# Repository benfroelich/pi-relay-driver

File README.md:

# 3.3V control relay driver board for switching light AC/DC loads

https://oshpark.com/shared_projects/c22zDmKN

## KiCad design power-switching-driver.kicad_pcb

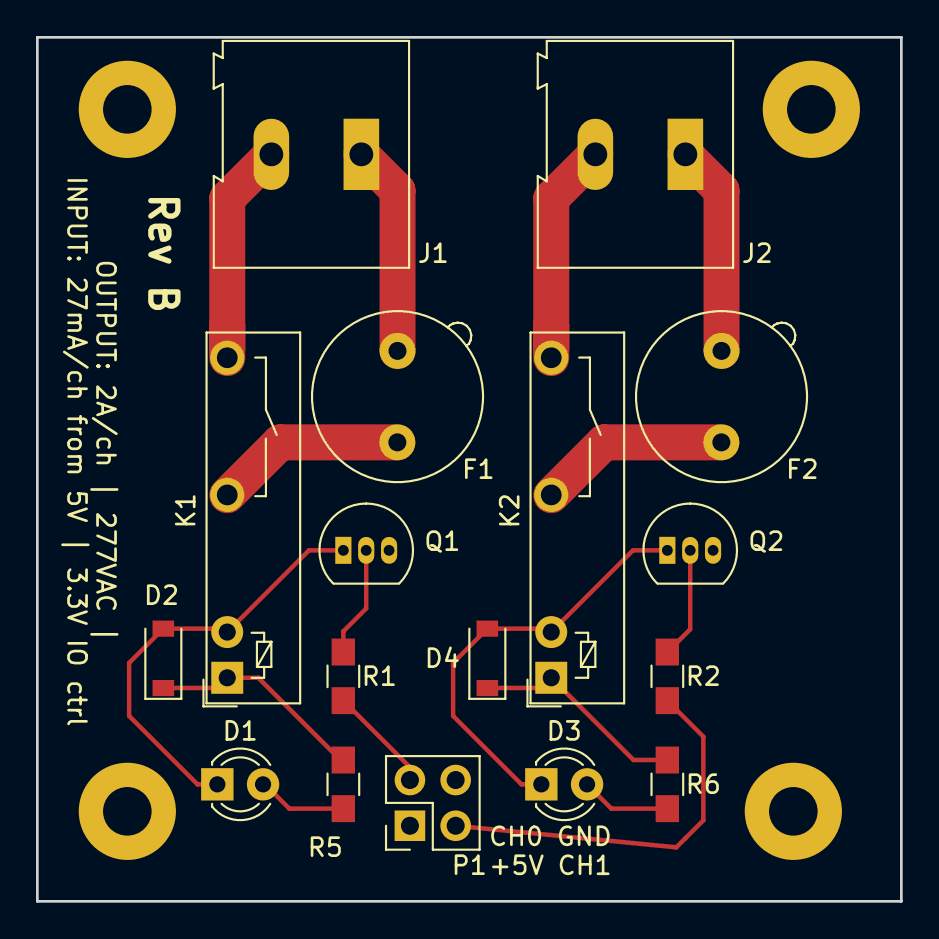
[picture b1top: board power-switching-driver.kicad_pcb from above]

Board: 2 copper layers, 48.0 x 48.0 mm, 17 parts (0 on the bottom side), 16 nets.

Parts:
D1, D3: LED; LED_D3.0mm
D2, D4: D; D_SOD-123
F1, F2: FUSE; Fuseholder_Fuse_TR5_Littlefuse-No560_No460
J1, J2: Screw_Terminal_1x02; TerminalBlock_Altech_AK300-2_P5.00mm
K1, K2: RELAY; Relay_SPST_TE_PCN-1xxD3MHZ
P1: CONN_02X02; Pin_Header_Straight_2x02_Pitch2.54mm
Q1, Q2: 2N2222; TO-92_Inline_Narrow_Oval
R1, R2: 240Ω; R_0805_HandSoldering
R5, R6: 2.2kΩ; R_0805_HandSoldering

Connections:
+5V: D2.1, D4.1, K1.1, K2.1, P1.1, R5.1, R6.1
/CH0_IN: P1.2, R1.2
/CH1_IN: P1.3, R2.2
GND: P1.4, Q1.3, Q2.3
unnamed: D1.1, D2.2, K1.2, Q1.1
unnamed: D1.2, R5.2
unnamed: D3.1, D4.2, K2.2, Q2.1
unnamed: D3.2, R6.2
unnamed: F1.1, K1.3
unnamed: F1.2, J1.1
unnamed: F2.1, K2.3
unnamed: F2.2, J2.1
unnamed: J1.2, K1.4
unnamed: J2.2, K2.4
unnamed: Q1.2, R1.1
unnamed: Q2.2, R2.1

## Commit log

2018-09-24 initial commit :)
2018-09-24 add GPL
2019-01-28 fix gitignore (ignore rescue-backup dir) and add pdf of sch
2019-02-10 use updated footprint locally until pull request comes through
2019-02-10 cleanup
2019-02-10 fix typo
2019-02-10 fix readme typo
2019-03-17 use official footprint libs
